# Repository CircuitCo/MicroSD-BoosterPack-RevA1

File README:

The microSD BoosterPack allows you to add mass storage to your Launchpad design for data logging and program storage.  The design uses the Launchpad's SPI interface to communicate with the microSD card. Jumper blocks are provided to set which GPIOs are used for the microSD card's chip select and card detect signals. The board is equipped with stackable connectors, which means it can be used with other BoosterPacks. The Micro SD BoosterPack is compatible with the MSP430 LaunchPad, Tiva C LaunchPad (previously Stellaris). This board is designed by Sakoman Inc. For more information on the designer, please visit http://www.sakoman.com/.

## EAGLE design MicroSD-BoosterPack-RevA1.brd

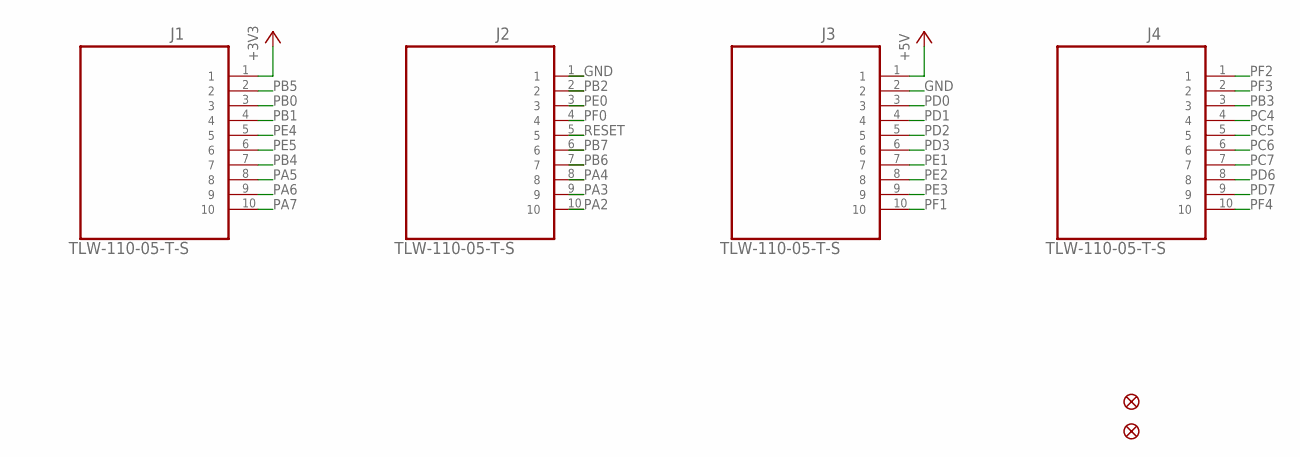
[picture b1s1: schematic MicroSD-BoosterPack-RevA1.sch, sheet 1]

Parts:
FID1, FID2: FIDUCIAL1X2; FIDUCIAL-1X2
J1: TLW-110-05-T-S; SAMTEC_TLW-110-05-T-S
J2, J3, J4: TLW-110-05-T-S; SAMTEC_TLW-110-05-T-S; MPN TLW-110-05-T-S

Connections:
+3V3: J1.1; also elsewhere on the board
+5V: J3.1
GND: J2.1, J3.2; also elsewhere on the board
PA2: J2.10; also elsewhere on the board
PA3: J2.9; also elsewhere on the board
PA4: J2.8; also elsewhere on the board
PA5: J1.8; also elsewhere on the board
PA6: J1.9; also elsewhere on the board
PA7: J1.10; also elsewhere on the board
PB0: J1.3
PB1: J1.4
PB2: J2.2
PB3: J4.3
PB4: J1.7; also elsewhere on the board
PB5: J1.2
PB6: J2.7; also elsewhere on the board
PB7: J2.6; also elsewhere on the board
PC4: J4.4
PC5: J4.5
PC6: J4.6
PC7: J4.7
PD0: J3.3
PD1: J3.4
PD2: J3.5
PD3: J3.6
PD6: J4.8
PD7: J4.9
PE0: J2.3; also elsewhere on the board
PE1: J3.7
PE2: J3.8
PE3: J3.9
PE4: J1.5; also elsewhere on the board
PE5: J1.6
PF0: J2.4
PF1: J3.10
PF2: J4.1
PF3: J4.2
PF4: J4.10
RESET: J2.5

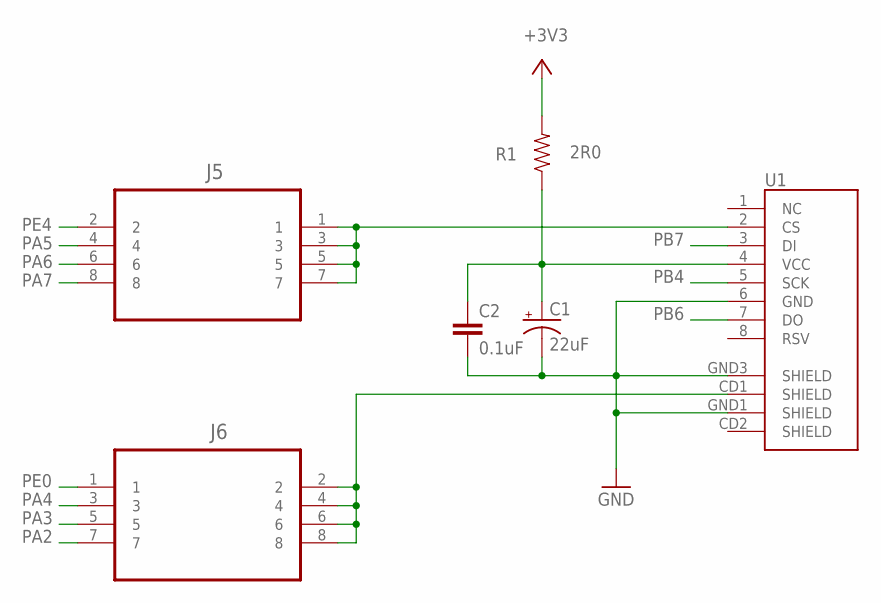
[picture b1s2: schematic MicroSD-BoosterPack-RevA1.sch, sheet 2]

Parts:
C1: 22uF; EIA3216
C2: 0.1uF; 0603-CAP
J5, J6: SLW-104-01-T-D; SAMTEC_SLW-104-01-T-D
R1: 2R0; 0603-RES
U1: USD-SOCKETNEW; MICRO-SD-SOCKET-PP

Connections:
+3V3: R1.2; also elsewhere on the board
+3V3F: C1.A (+), C2.1, R1.1, U1.4 (VCC)
GND: C1.C (-), C2.2, U1.6 (GND), U1.GND1 (SHIELD), U1.GND3 (SHIELD); also elsewhere on the board
unnamed: J6.2, J6.4, J6.6, J6.8, U1.CD1 (SHIELD)
unnamed: J5.1, J5.3, J5.5, J5.7, U1.2 (CS)
PA2: J6.7; also elsewhere on the board
PA3: J6.5; also elsewhere on the board
PA4: J6.3; also elsewhere on the board
PA5: J5.4; also elsewhere on the board
PA6: J5.6; also elsewhere on the board
PA7: J5.8; also elsewhere on the board
PB4: U1.5 (SCK); also elsewhere on the board
PB6: U1.7 (DO); also elsewhere on the board
PB7: U1.3 (DI); also elsewhere on the board
PE0: J6.1; also elsewhere on the board
PE4: J5.2; also elsewhere on the board

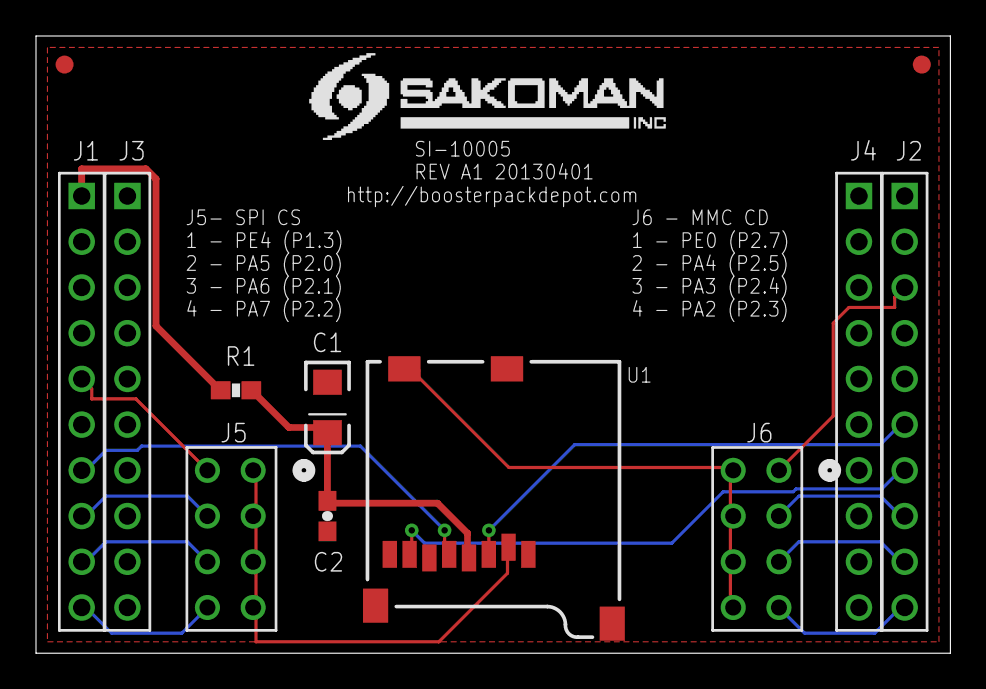
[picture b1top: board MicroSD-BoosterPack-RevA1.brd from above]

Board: 2 copper layers, 50.8 x 34.3 mm, 12 parts (0 on the bottom side), 16 nets.

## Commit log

2013-09-11 init-commit
2013-09-11 update-docs

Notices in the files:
parts and their libraries:
SparkFun-Connectors: Licensing: CC v3.0 Share-Alike You are welcome to use this library for commercial purposes.
